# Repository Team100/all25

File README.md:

----
----
----
----
----

<pre>
 █████╗ ██████╗  ██████╗██╗  ██╗██╗██╗   ██╗███████╗██████╗ 
██╔══██╗██╔══██╗██╔════╝██║  ██║██║██║   ██║██╔════╝██╔══██╗
███████║██████╔╝██║     ███████║██║██║   ██║█████╗  ██║  ██║
██╔══██║██╔══██╗██║     ██╔══██║██║╚██╗ ██╔╝██╔══╝  ██║  ██║
██║  ██║██║  ██║╚██████╗██║  ██║██║ ╚████╔╝ ███████╗██████╔╝
╚═╝  ╚═╝╚═╝  ╚═╝ ╚═════╝╚═╝  ╚═╝╚═╝  ╚═══╝  ╚══════╝╚═════╝ 
                                                            
</pre>

The 2025 code is read-only.  You can find current development in the "all26" repo.

----
----
----
----
----

# all25

What's here:

* **comp**: RoboRIO competition code for 2025
* **console**: Button board hardware and code
* **doc**: Documentation: look here for instructions!
* **lib**: Evergreen RoboRIO library code
* **raspberry_pi** Coprocessor tasks: vision, logging, GTSAM
* **studies**: Small independent projects
  * Your project
  * Another project
  * etc ...

all25 contains *all* the Team 100 code for *2025.*  There's just one repository,
so that sharing library code across projects is easier.

This style of code management is sometimes called a ["monorepo"](https://en.wikipedia.org/wiki/Monorepo) if you want to read more about it.

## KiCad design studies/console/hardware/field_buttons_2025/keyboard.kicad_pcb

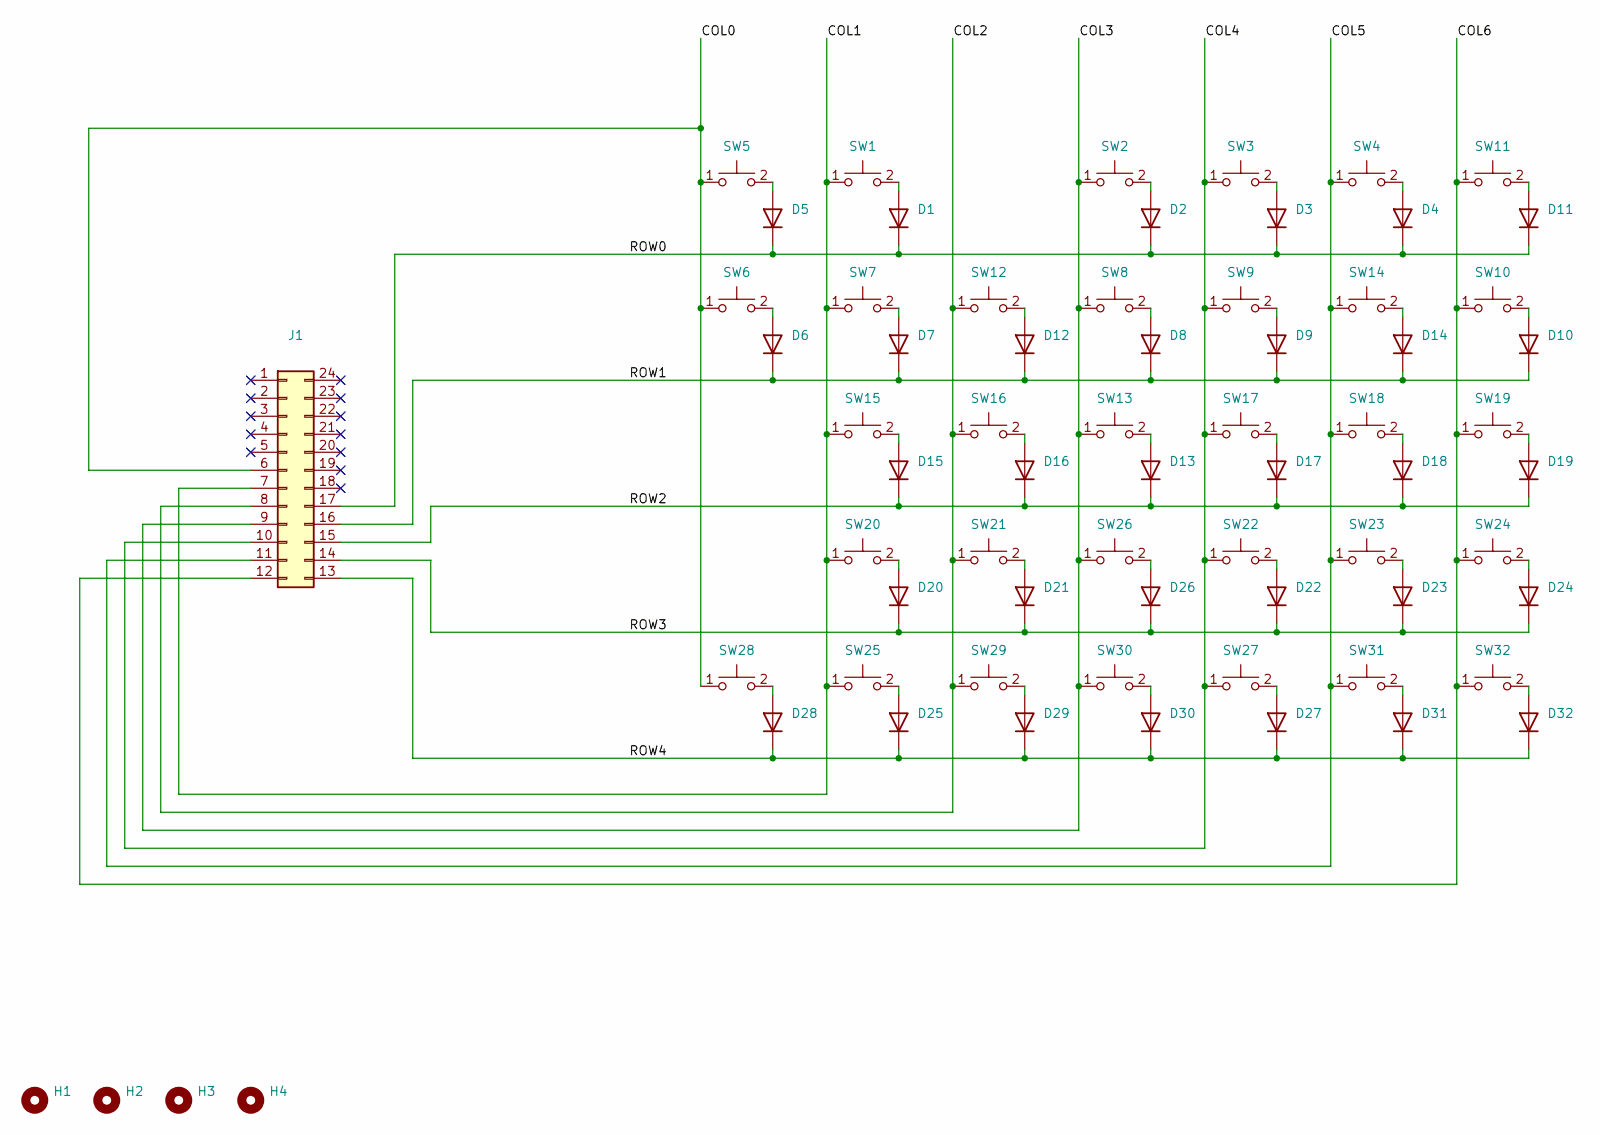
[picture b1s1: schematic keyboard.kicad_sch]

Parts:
D1, D2, D3, D4, D5, D6, D7, D8, D9, D10, D11, D12, D13, D14, D15, D16, D17, D18, D19, D20, D21, D22, D23, D24, D25, D26, D27, D28, D29, D30, D31, D32: D; D_DO-35_SOD27_P10.16mm_Horizontal
H1, H2, H3, H4: MountingHole_4.3mm_M4_ISO7380_Pad
J1: Conn_02x12_Counter_Clockwise; DIP-24_W15.24mm_Socket
SW1, SW2, SW3, SW4, SW5, SW6, SW7, SW8, SW9, SW10, SW11, SW12, SW13, SW14, SW15, SW16, SW17, SW18, SW19, SW20, SW21, SW22, SW23, SW24, SW25, SW26, SW27, SW28, SW29, SW30, SW31, SW32: SW_Push; SW_Cherry_MX_PCB_1.00u

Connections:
/COL0: J1.6, SW5.1, SW6.1, SW28.1
/COL1: J1.7, SW1.1, SW7.1, SW15.1, SW20.1, SW25.1
/COL2: J1.8, SW12.1, SW16.1, SW21.1, SW29.1
/COL3: J1.9, SW2.1, SW8.1, SW13.1, SW26.1, SW30.1
/COL4: J1.10, SW3.1, SW9.1, SW17.1, SW22.1, SW27.1
/COL5: J1.11, SW4.1, SW14.1, SW18.1, SW23.1, SW31.1
/COL6: J1.12, SW10.1, SW11.1, SW19.1, SW24.1, SW32.1
/ROW0: D1.1 (K), D2.1 (K), D3.1 (K), D4.1 (K), D5.1 (K), D11.1 (K), J1.17
/ROW1: D6.1 (K), D7.1 (K), D8.1 (K), D9.1 (K), D10.1 (K), D12.1 (K), D14.1 (K), J1.16
/ROW2: D13.1 (K), D15.1 (K), D16.1 (K), D17.1 (K), D18.1 (K), D19.1 (K), J1.15
/ROW3: D20.1 (K), D21.1 (K), D22.1 (K), D23.1 (K), D24.1 (K), D26.1 (K), J1.14
/ROW4: D25.1 (K), D27.1 (K), D28.1 (K), D29.1 (K), D30.1 (K), D31.1 (K), D32.1 (K), J1.13
unnamed: D1.2 (A), SW1.2
unnamed: D2.2 (A), SW2.2
unnamed: D3.2 (A), SW3.2
unnamed: D4.2 (A), SW4.2
unnamed: D5.2 (A), SW5.2
unnamed: D6.2 (A), SW6.2
unnamed: D7.2 (A), SW7.2
unnamed: D8.2 (A), SW8.2
unnamed: D9.2 (A), SW9.2
unnamed: D10.2 (A), SW10.2
unnamed: D11.2 (A), SW11.2
unnamed: D12.2 (A), SW12.2
unnamed: D13.2 (A), SW13.2
unnamed: D14.2 (A), SW14.2
unnamed: D15.2 (A), SW15.2
unnamed: D16.2 (A), SW16.2
unnamed: D17.2 (A), SW17.2
unnamed: D18.2 (A), SW18.2
unnamed: D19.2 (A), SW19.2
unnamed: D20.2 (A), SW20.2
unnamed: D21.2 (A), SW21.2
unnamed: D22.2 (A), SW22.2
unnamed: D23.2 (A), SW23.2
unnamed: D24.2 (A), SW24.2
unnamed: D25.2 (A), SW25.2
unnamed: D26.2 (A), SW26.2
unnamed: D27.2 (A), SW27.2
unnamed: D28.2 (A), SW28.2
unnamed: D29.2 (A), SW29.2
unnamed: D30.2 (A), SW30.2
unnamed: D31.2 (A), SW31.2
unnamed: D32.2 (A), SW32.2

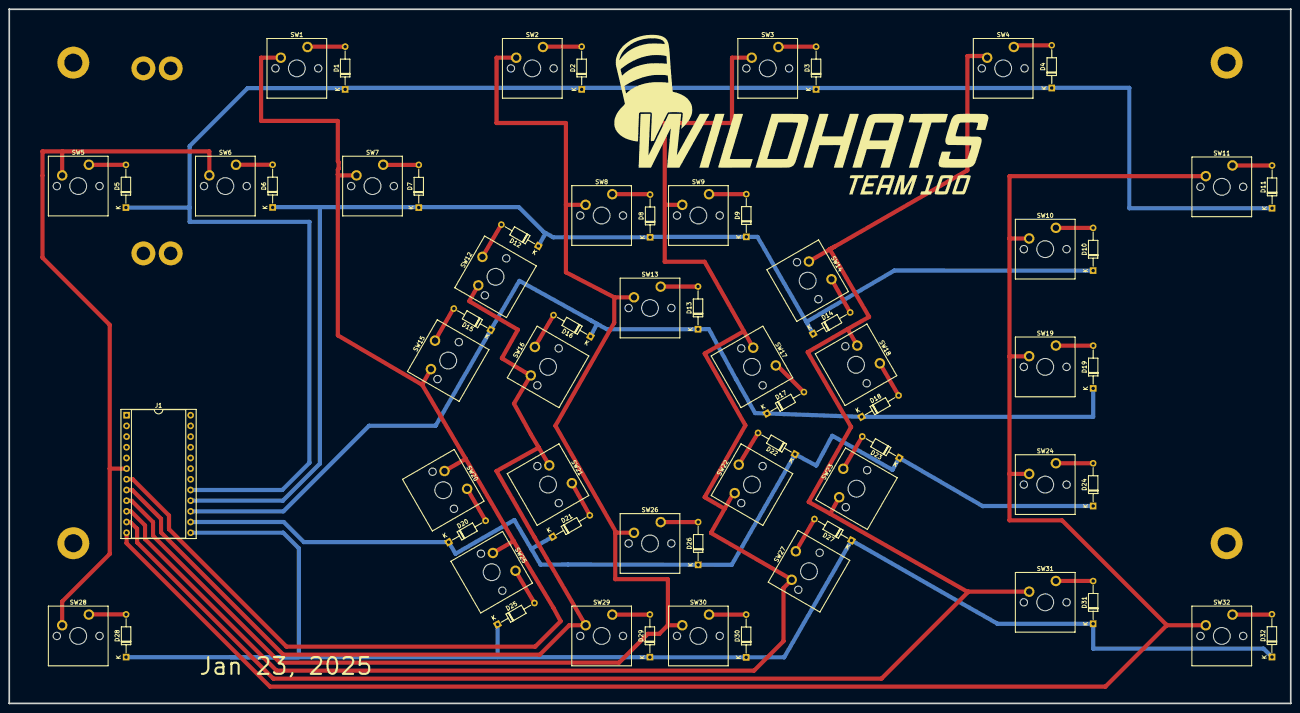
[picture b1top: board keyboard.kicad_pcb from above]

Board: 2 copper layers, 304.8 x 165.1 mm, 73 parts (0 on the bottom side), 44 nets.

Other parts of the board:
H5, H6, H7, H8: MountingHole_3.2mm_M3_ISO7380_Pad

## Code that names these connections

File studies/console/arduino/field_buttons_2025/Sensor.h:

#ifndef SENSOR_H
#define SENSOR_H
#include "Data.h"

// The left side of the board is columns,
// the right side of the board is rows.
constexpr uint8_t COL0 = 3; // DIP pin 6
constexpr uint8_t COL1 = 9; // DIP pin 12
constexpr uint8_t COL2 = 8; // DIP pin 11
constexpr uint8_t COL3 = 7; // DIP pin 10
constexpr uint8_t COL4 = 6; // DIP pin 9
constexpr uint8_t COL5 = 5; // DIP pin 8
constexpr uint8_t COL6 = 4; // DIP pin 7
constexpr uint8_t ROW0 = A0; // DIP pin 17
constexpr uint8_t ROW1 = 15; // DIP pin 16
constexpr uint8_t ROW2 = 14; // DIP pin 15
constexpr uint8_t ROW3 = 16; // DIP pin 14
constexpr uint8_t ROW4 = 10; // DIP pin 13

/**
 * We use a 7x5 grid with three holes, resulting in 32 buttons.
 */
class Sensor {
public:
  /**
   * Set pin modes.
   */
  void initialize() {
    // All columns are pull-up digital inputs.
    pinMode(COL0, INPUT_PULLUP);
    pinMode(COL1, INPUT_PULLUP);
    pinMode(COL2, INPUT_PULLUP);
    pinMode(COL3, INPUT_PULLUP);
    pinMode(COL4, INPUT_PULLUP);
    pinMode(COL5, INPUT_PULLUP);
    pinMode(COL6, INPUT_PULLUP);
    // All rows start as high-Z digital inputs.
    rowHigh(ROW0);
    rowHigh(ROW1);
    rowHigh(ROW2);
    rowHigh(ROW3);
    rowHigh(ROW4);
  }

  /**
   * Pull the row low
   */
  void rowLow(uint8_t pin) {
    pinMode(pin, OUTPUT);
    digitalWrite(pin, LOW);
    delayMicroseconds(5);
  }

  /**
   * Set the row back to high-Z
   */
  void rowHigh(uint8_t pin) {
    pinMode(pin, INPUT);
    delayMicroseconds(5);
  }

  /**
   * Return true if col is pulled low, i.e. key is pressed.
   */
  boolean colRead(uint8_t pin) {
    return digitalRead(pin) == LOW;
  }

  /**
   * Reads the key array state and writes the values into reportTx.
   */
  void sense(ReportTx& reportTx) {
    rowLow(ROW0);
    reportTx.b1 = colRead(COL0);
    reportTx.b2 = colRead(COL1);
    // note missing col2
    reportTx.b3 = colRead(COL3);
    reportTx.b4 = colRead(COL4);
    reportTx.b5 = colRead(COL5);
    reportTx.b6 = colRead(COL6);
    rowHigh(ROW0);
    rowLow(ROW1);
    reportTx.b7 = colRead(COL0);
    reportTx.b8 = colRead(COL1);
    reportTx.b9 = colRead(COL2);
    reportTx.b10 = colRead(COL3);
    reportTx.b11 = colRead(COL4);
    reportTx.b12 = colRead(COL5);
    reportTx.b13 = colRead(COL6);
    rowHigh(ROW1);
    rowLow(ROW2);
    // note missing col0
    reportTx.b14 = colRead(COL1);
    reportTx.b15 = colRead(COL2);
    reportTx.b16 = colRead(COL3);
    reportTx.b17 = colRead(COL4);
    reportTx.b18 = colRead(COL5);
    reportTx.b19 = colRead(COL6);
    rowHigh(ROW2);
    rowLow(ROW3);
    // note missing col0
    reportTx.b20 = colRead(COL1);
    reportTx.b21 = colRead(COL2);
    reportTx.b22 = colRead(COL3);
    reportTx.b23 = colRead(COL4);
    reportTx.b24 = colRead(COL5);
    reportTx.b25 = colRead(COL6);
    rowHigh(ROW3);
    rowLow(ROW4);
    reportTx.b26 = colRead(COL0);
    reportTx.b27 = colRead(COL1);
    reportTx.b28 = colRead(COL2);
    reportTx.b29 = colRead(COL3);
    reportTx.b30 = colRead(COL4);
    reportTx.b31 = colRead(COL5);
    reportTx.b32 = colRead(COL6);
    rowHigh(ROW4);
  }

};
#endif  // SENSOR_H

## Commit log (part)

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2025-02-18 remove steering related limiters
    i'm not convinced they ever did anything useful; in any case i don't think they're worth keeping.
2025-02-18 more chopping in the setpoint generator
2025-02-19 help im stuck outside
2025-02-19 kinodynamic limiter is now field relative
2025-02-19 cleaning
2025-02-19 add simulation for elevator, just so simulation works
2025-02-19 Work from messing around
2025-02-19 i added accel and the elevator sucks
2025-02-20 fix the build
2025-02-20 fiddling with elevator visualization
2025-02-20 i finished. ahah. pls. we are NEVER using this
2025-02-20 add steering -> driving velocity correction
    i'm not sure this is right at all
2025-02-21 Changes from tdday
2025-02-21 jerk limiter and deadband, doesn't work yet.
2025-02-21 tUNIN
2025-02-22 study for jerk limiting etc
2025-02-22 removed TimedCache, use Memo instead.
2025-02-22 fix git mistake
2025-02-22 fix timed cache study build
2025-02-22 move UDP logging to a study.
    it's too late to start using it
2025-02-22 speed up unit tests
2025-02-23 add diagnostics for roborio 1.0 memory
2025-02-23 add a timer for memo updates
2025-02-23 improve holonomic spline theta
    now holonomic splines use average theta speed as the theta endpoint; previously they used zero, which would cause little hiccups in the theta reference at each spline boundary along a path.
2025-02-24 found some issues in holonomic splines and trajectories, WIP
2025-02-24 fix holonomic path omega
    previously omega was forced to zero at segment boundaries; now, instead, omega is allowed to be discontinuous. if the omega rate isn't too high, the discontinuities shouldn't be that big a deal.
2025-02-24 fix the build and add simulated wrist so that the simulator doesn't crash on startup
2025-02-26 extension and roller code tested and working
2025-02-26 made but not checked or tested current limiter
2025-02-26 Profile control
2025-02-27 Work from today
2025-02-27 fixed simulation button mappings
2025-03-02 don't print anything
2025-03-02 remove some stale TODO's
2025-03-03 add experiment for unprofiled steering control
2025-03-03 move button board to top level
2025-03-03 add arduino MCP23017 library
2025-03-03 rename field buttons to key array
2025-03-03 moving-entry trajectories
2025-03-03 dynamic capsize limit
2025-03-04 Cameras
2025-03-04 reset caches on encoder reset
2025-03-04 invert buttons, reduce delay
2025-03-04 add holonomic pose for spline/path/trajectory making
2025-03-04 Fix offsets
2025-03-04 simplifying trajectories
2025-03-05 more about trajectories
2025-03-05 buncha changes. keep up to date. more subsystems to add. somehow the carraige sparks are linked? new CAN IDs and swerve works maybe
2025-03-05 lots of different ways to do auto. hopefully one of them works
2025-03-05 arduino libs update
2025-03-06 Added variable elevator constants
2025-03-06 add feedforward decel
2025-03-06 changes. very very bad super structure code for a very very bad wrist. ill chage it later. dont jail me
2025-03-07 button boards done
2025-03-07 button board interface class. use port TWO
2025-03-07 better warning for gyro staleness
2025-03-07 make moving-entry spline shape use the initial speed
2025-03-08 yes i fixed it. EPA. wrist bad. tune drivetrain time. i hate it i hate it i hate it i hate it i hate it
2025-03-08 Worrk from epa
2025-03-08 higher center of mass
2025-03-08 make a note about VCG in kinodynamics constructor
2025-03-08 Fix offset
2025-03-08 make rotary mechanism limits mutable
2025-03-08 Fixed offsets
2025-03-09 reference controller initializes on execute
2025-03-09 feedwoward updates
2025-03-09 exploring trajectory performance
2025-03-09 trajectory generation performance improvement
    overruns once at startup, then not anymore.
    also added support for running without hardware attatched.
2025-03-09 fix the banner
2025-03-10 fix tests
2025-03-10 typo
2025-03-11 Algaue
2025-03-11 changes. so much more work to be done. its over
2025-03-11 some more changes. whoops. this is supposed to allow a supplier to select the scoring level. first part of the sequential drives to spot. second part initializes, checks the supplier, and figures out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
2025-03-11 fix tip
2025-03-11 added more things
2025-03-12 swap PI
2025-03-12 ball shooter demo
2025-03-12 made sim joystick rotation work
2025-03-12 turn off camera offset output
2025-03-12 make AlgaeGrip not crash simulation
2025-03-12 turned on AntiJitter and CrossTrackError fix by default, and softened the vision updates by a factor of 2.
2025-03-13 fix the build, clean up a bit
2025-03-13 DriveToBarge
2025-03-13 Fix build
2025-03-13 Neatening
2025-03-13 Climb
2025-03-13 TODO
2025-03-13 more small
2025-03-13 Try this maybe
2025-03-13 add normally-closed limit switch config
2025-03-13 more changes L3 almost works
2025-03-14 changed a bunch of shit. most certainly broke things. i hurt i jurt i hurt
2025-03-15 remove velocity from rio sensors, the log says it's crap
2025-03-15 add sensor-is-connected log
2025-03-15 reduce frequency threshold for encoder
2025-03-15 lots of changes. maybe dont accept a pr? i changed auto to have a looser tolerance. i think that was the issue
2025-03-15 fix vision test for new softer vision constants
2025-03-15 Added to go processor
2025-03-15 joel can look at this and see whats wrong?
2025-03-16 more changes over day 2. we're cooked
2025-03-16 push. GUESS
2025-03-16 before playoffs works
2025-03-19 after svr
2025-03-20 add wrist visualization
2025-03-20 organize imports
2025-03-20 log blank when composite is done
2025-03-20 added logging to the swerve limiter
2025-03-20 make the vision "heed" limit adjustable
    manual driving sets it very high (see everything)
    embark sets it very low (see just the near tag)
2025-03-20 working on simulated cameras
2025-03-21 progress on simulated camera
2025-03-21 fix simulated alliance test
2025-03-21 simulated tag detector tag visibility seems correct now
2025-03-22 simulated camera WIP
2025-03-22 more changes push barge works
2025-03-22 more vision cleaning
2025-03-22 Sim fixed for limit switches and servoangle1
2025-03-22 more vision
2025-03-22 more changes. i added smart place go up while moving. and led mgiht work now
2025-03-23 make the simulated cameras actually work
    use a network tables client, then the timestamp works.
    also publish "all" and "just the ones used for pose" separately.
2025-03-23 make simulated tags use previous poses as reference
2025-03-23 add advantagescope layout
2025-03-23 test robot init, periodic, etc
2025-03-23 fix comp tests
2025-03-23 add logger names for groups
2025-03-24 poking at the swerve limiters, seems fine
2025-03-24 3 coral auto for my experimentation, commenting
2025-03-24 add exponential profile and combined profile
2025-03-24 working on limited exponential profile
2025-03-25 selectable axis profiles for holonomic profile
2025-03-25 add logging to commands
2025-03-25 servo reset() methods now zero velocity
2025-03-25 revive jerk-limited profiles
2025-03-25 timed profile and two implementations
2025-03-26 made the safe position stay safe
2025-03-26 more changes. new wrist and LEDs
2025-03-26 Trust this works
2025-03-26 Uh whoops
    This works trust
2025-03-26 Update Coral2Auto.java
    More fixing
2025-03-26 Revert
    Revert
2025-03-26 many profile choices for wrist2
2025-03-26 fix mistake in wrist2
2025-03-26 recent changes. scoreing maybe faster? changes some logging levels
2025-03-27 try to fix the tests
2025-03-27 fix timed wrist profiles
2025-03-27 add "profileDone" for command finished
2025-03-27 wrist kind of works now. mabe the new profiles will come in clutch
2025-03-28 auto run on corners TEST LATER
2025-03-28 fixes
    Fixes
2025-03-28 make elevator profile adjustable on the fly too
2025-03-28 fix imports
2025-03-28 error is zero prior to encoder sync
2025-03-28 make onboard/outboard wrist control selectable using a constant
2025-03-29 fix crasher for zero-duration septic splines
2025-03-29 lots of changes. working on auto and fixing default commands and profile bugs
2025-03-29 Update Coral2Auto.java
    merge
2025-03-30 spline tests and advantagescope layout
2025-03-30 setpoints data test
2025-03-31 fix spline tests even though we're not using it
2025-03-31 turn off "my table" network table
2025-03-31 remind myself what logging levels do
2025-03-31 stop logging temperature and torque-current
2025-03-31 connect to the JMX server via 10.1.0.2.
2025-03-31 increase vision buffer depth to avoid missing updates
2025-03-31 don't spam the log with slack time messages
2025-03-31 remove one thing from comp log level
2025-04-01 moved some constants into lib to fix the build
2025-04-01 default swerve limiter off
2025-04-01 updates from EPA, fixed barge approach
2025-04-01 fix tip whoops
2025-04-01 remove unused stuff in wrist2.java
2025-04-01 turn down console spam
2025-04-01 imported comp to 2025.3.2
2025-04-01 imported lib to 2025.3.2
2025-04-01 couple small changes. bind climb
2025-04-02 add parking lot study
2025-04-02 move stuff from "for testing" to the parking lot study
2025-04-02 increase main thread priority. NEEDS TESTING.
2025-04-02 maybe JIT warming is the cause of slack time
2025-04-02 verify trajectory limits
2025-04-02 turned off perf stuff that seemed not to work
2025-04-03 focus test rig
2025-04-03 cvr ready. aydan is my king. the glaze is real. im pregnant
2025-04-04 push changes for joel
2025-04-08 fast/slow profiles
2025-04-08 remove dual profiles
    it's just too fiddly. make custom profiles instead.
2025-04-08 used roadrunner dynamic profile for jerk-limiting at the goal only
2025-04-08 cleaning roadrunner profiles
2025-04-09 get rid of "pair"
2025-04-09 cleaning roadrunner
2025-04-09 cleaning roadrunner dynamic profile
2025-04-09 make control and model into records
2025-04-09 make model and control interpolatable
2025-04-10 constant-accel with velo limit
2025-04-10 profile with max v
2025-04-10 distinct decel and accel
2025-04-10 jerk-limited goal path. looks good.
2025-04-10 made CompleteProfile actually work
2025-04-10 link to graphs
2025-04-11 remove steer-at-rest.
    not having it didn't seem to hurt our excellent navigation accuracy at CVR, so, it's simpler not to have it.
2025-04-11 remove unused logger
2025-04-12 removed combined encoders from servos, they're in the mechanism now
2025-04-12 refactoring the gravity servo
2025-04-12 working on the gravity thing
2025-04-12 removed gravity servo
2025-04-12 remove setpoint and goal getters from angular servos
2025-04-12 kinematics for the elevator/arm combination
2025-04-14 compiles
2025-04-14 pulling the profile out of the controller
2025-04-15 working on coordination
2025-04-15 added velocity to the coordinated path, now mostly works.
2025-04-15 viz separate from elevator class
2025-04-16 elevator accel feedforward for wrist
2025-04-16 working on teaching examples
2025-04-16 more teaching examples
2025-04-17 move unfinished spline stuff to a study
2025-04-17 fixed all the warnings
2025-04-22 simple state-based example
2025-04-22 add state time-out
2025-04-22 CVR changes from gold driver station
2025-04-23 simulated 6dof arm sequences with state machine
2025-04-23 more state machine examples
2025-04-24 illustrate the trigger bug
2025-04-25 new trigger without the bug
2025-04-28 fiddling with states
2025-05-06 arm demo board stuff
2025-05-10 initial commit with LEDs
2025-05-10 calibrator
2025-05-11 dummy calibrations
2025-05-11 moved arm 23 stuff to a study
2025-05-12 redoing 5dof arm kinematics
2025-05-12 5dof inv kinematics seems pretty good now
2025-05-12 working on visualizer
2025-05-13 fidling with viz
2025-05-13 3d arm visualizer works but isn't hooked up to the simulation
2025-05-13 forward kinematics returns all jionts now
2025-05-14 mostly working, shows a bug in the twist
2025-05-14 looking for the bug
2025-05-14 bad rotation now allowed
2025-05-14 two-dof version of arm control
2025-05-14 added URDF object model
2025-05-18 gradient descent
2025-05-19 coordinate descent
2025-05-20 newton's method
2025-05-22 a bit closer to arbitrary kinematic chains
2025-05-22 working on URDF
2025-05-23 URDF kinematics, not done
2025-05-23 URDF inverse kinematics, also fix tests
2025-08-30 lasercan code
2025-08-31 gitigingnore
    Just removed the git ignore
2025-09-24 Revert "integrated some of the manipulator code to the main robot code"
2025-09-27 upgrade gradle wrapper to 9.1.0
2025-12-28 trajectory recycling WIP
2025-12-29 trajectory recycler and soft start/end kinda work now
2025-12-29 remove timed profiles; we never use them.
